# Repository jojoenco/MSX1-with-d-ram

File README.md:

# MSX1-with-d-ram
MSX1 compatible machine with old fashion D-Ram

Specs:  
Z80  
TMS9918 (composiet out)  
8255  
AY-3-8910  
HM4816 X8 V-Ram  
HM4864 X8 Ram  
74xx  logic IC's  

Tested until version 2.5 
This is version 2.6 should work as I only removed the Opamp for audio out and chanced the Transistor for the (Cassete)relay that
probably nobody uses. (because there is also a jack in and out for the cassete)

What works and tested in version 2.5:
- [x] Boot with MSX-Bios and C-Bios 
- [x] Video Out
- [x] audio out (sound was bad in version 2.5 so removed Opamp in 2.6)
- [x] Joystick ports
- [x] cassete in through 3.5"mm jack
- [ ] cassete out not tested
- [ ] Cassete DIN not tested
- [ ] relay (for Cassete REM) did not switch in version 2.5 (chanced transistor but not tested yet)
- [x] reset
- [X] Keyboard 
- [X] Cartridge Slot 1 and Slot2
- [ ] Printer port not tested

Because there is only a matrix connection for the keyboard I used the keyboard from Sergey Kiselev (github.com/skiselev/omega) to test.
I used the keyboard without de chips on it because they are on the main board and I jumpered on U2 the pins 1-2 and 3-4 and 5-6 and 8-9.
And then connected the wires directly to U1 pin 1-9 and J1 the bottom row.

My own keyboard PCB is ready but I am waiting for the switches to test it.

THE KEYBOARD  
The switches came in and it works fine:  
https://github.com/jojoenco/Keyboard-for-MSX1-with-d-ram

Below a foto of version 2.0 

And more Below Version 2.6 with no components yet

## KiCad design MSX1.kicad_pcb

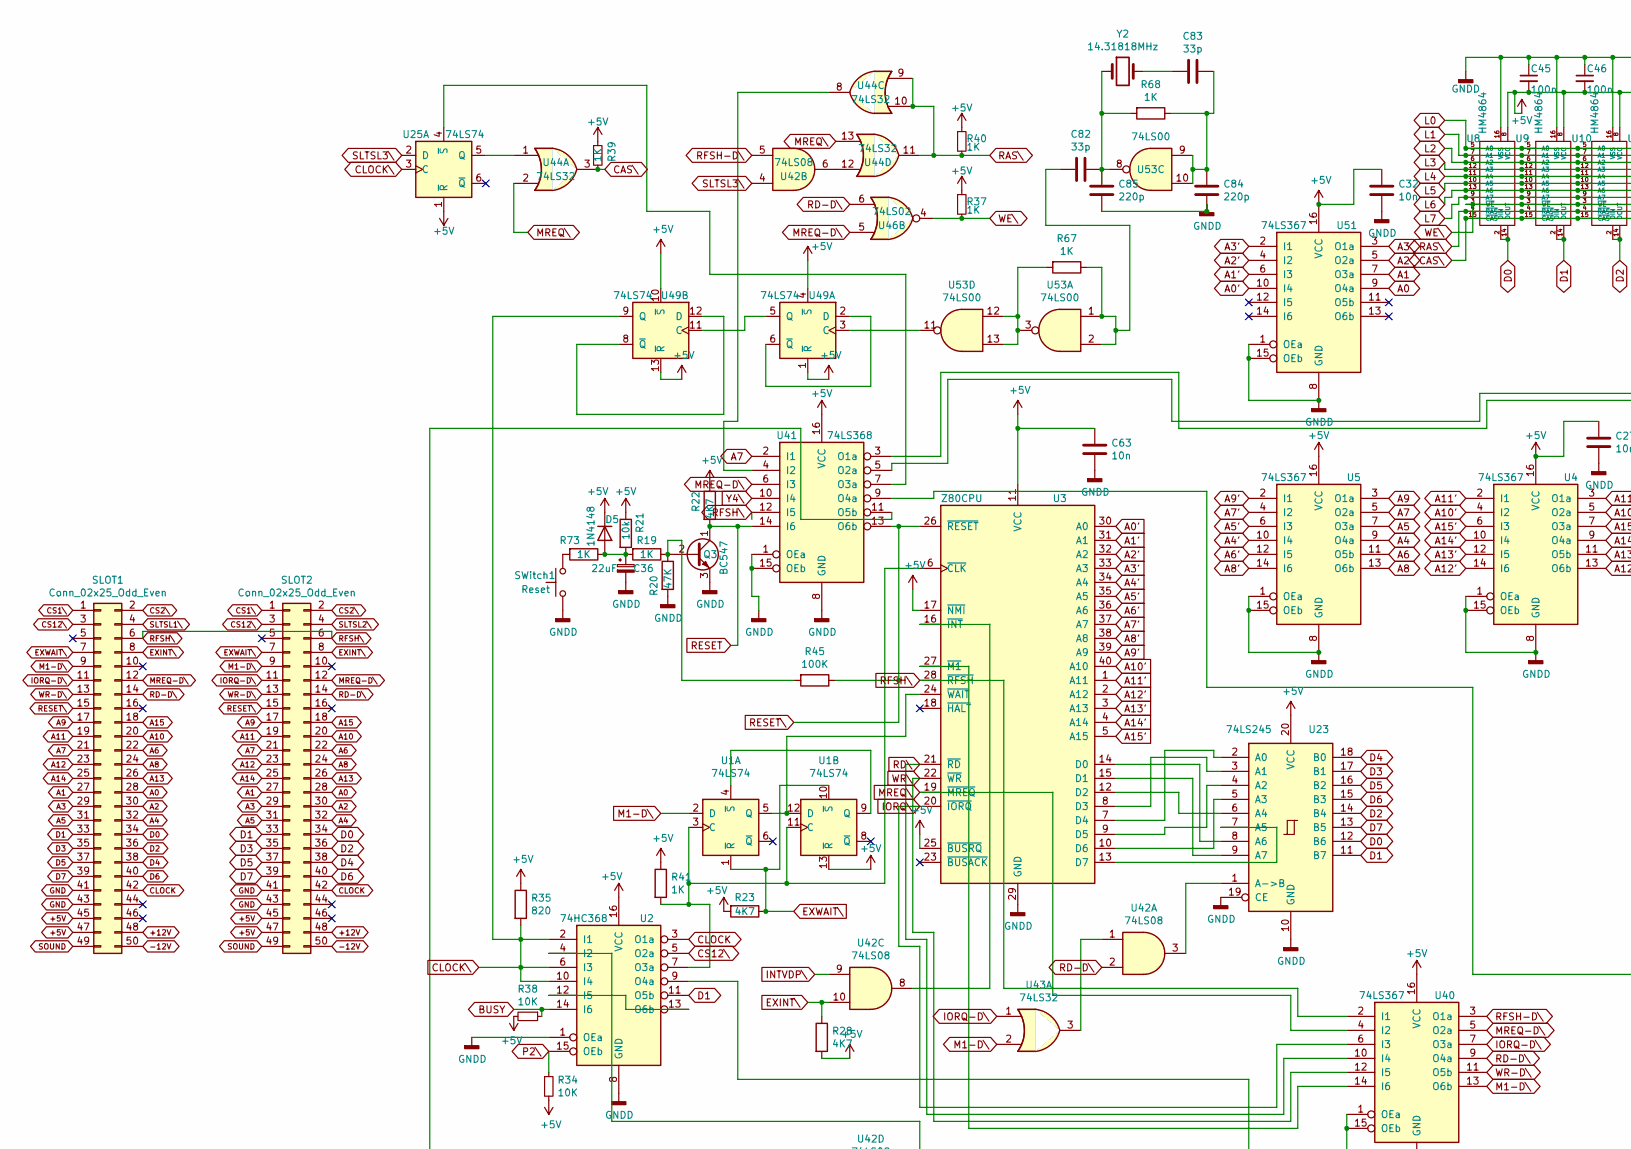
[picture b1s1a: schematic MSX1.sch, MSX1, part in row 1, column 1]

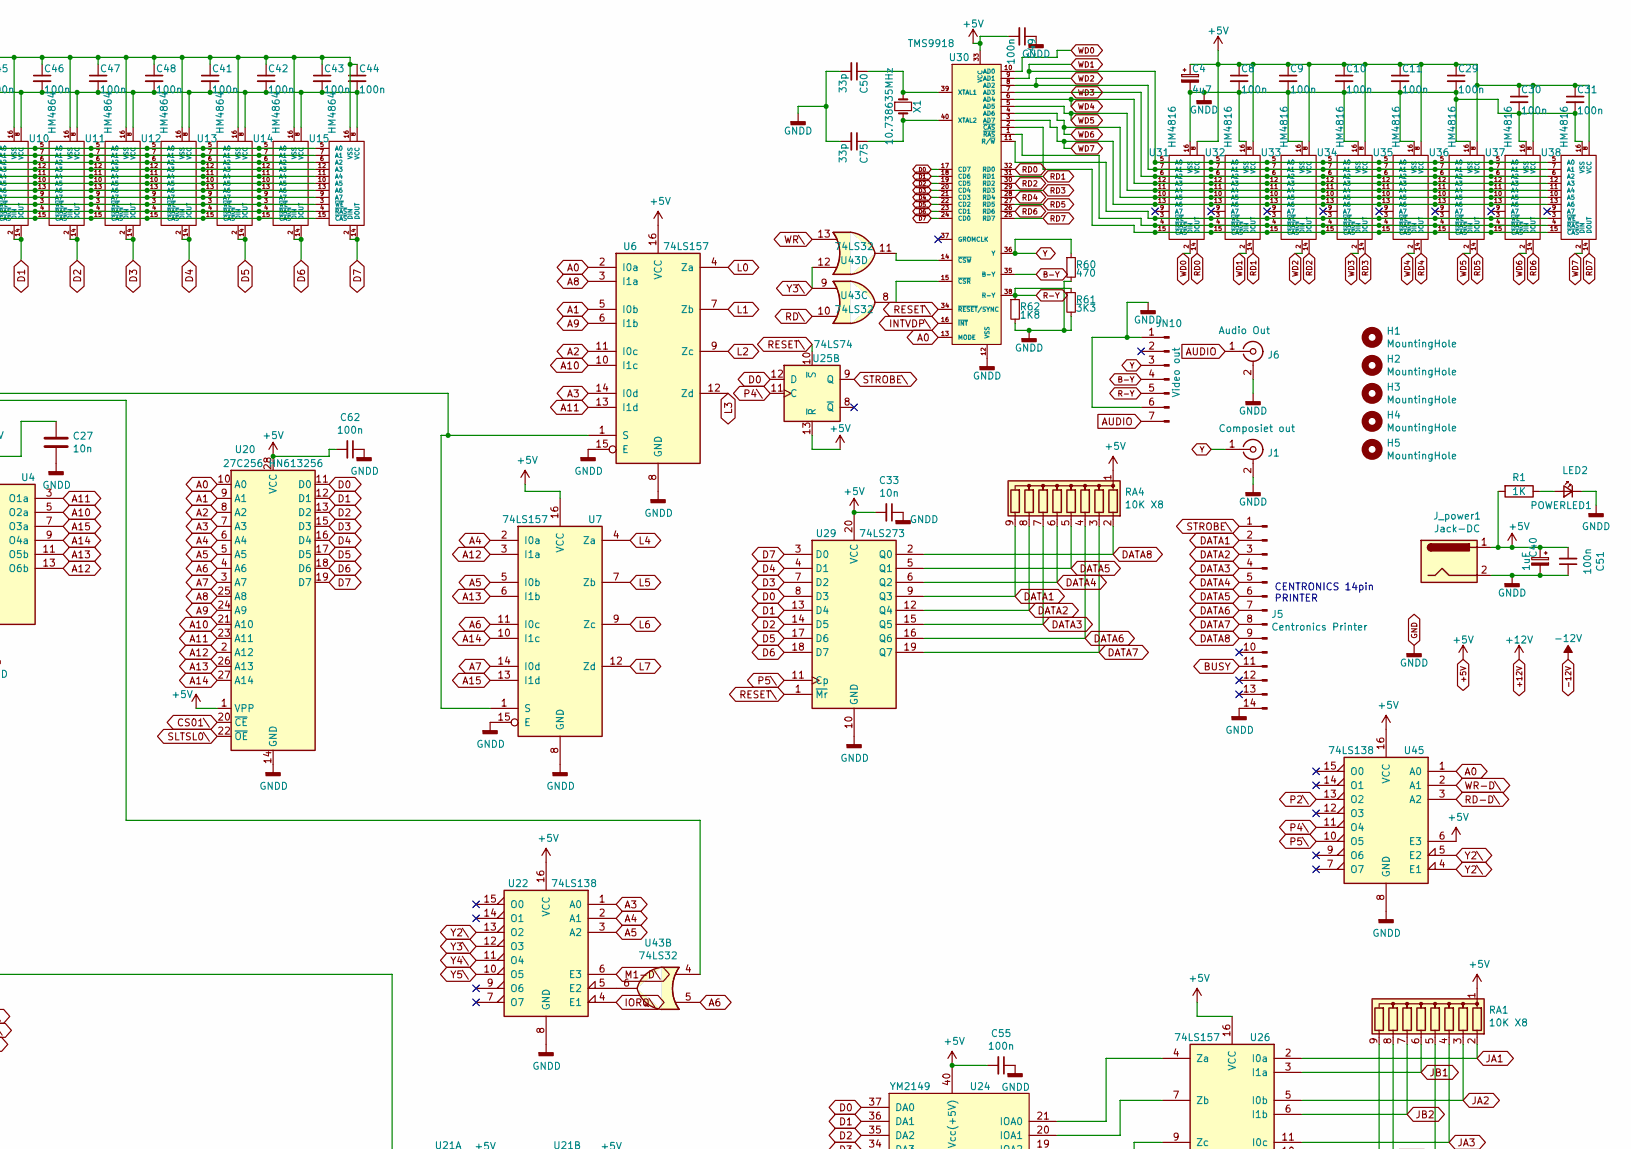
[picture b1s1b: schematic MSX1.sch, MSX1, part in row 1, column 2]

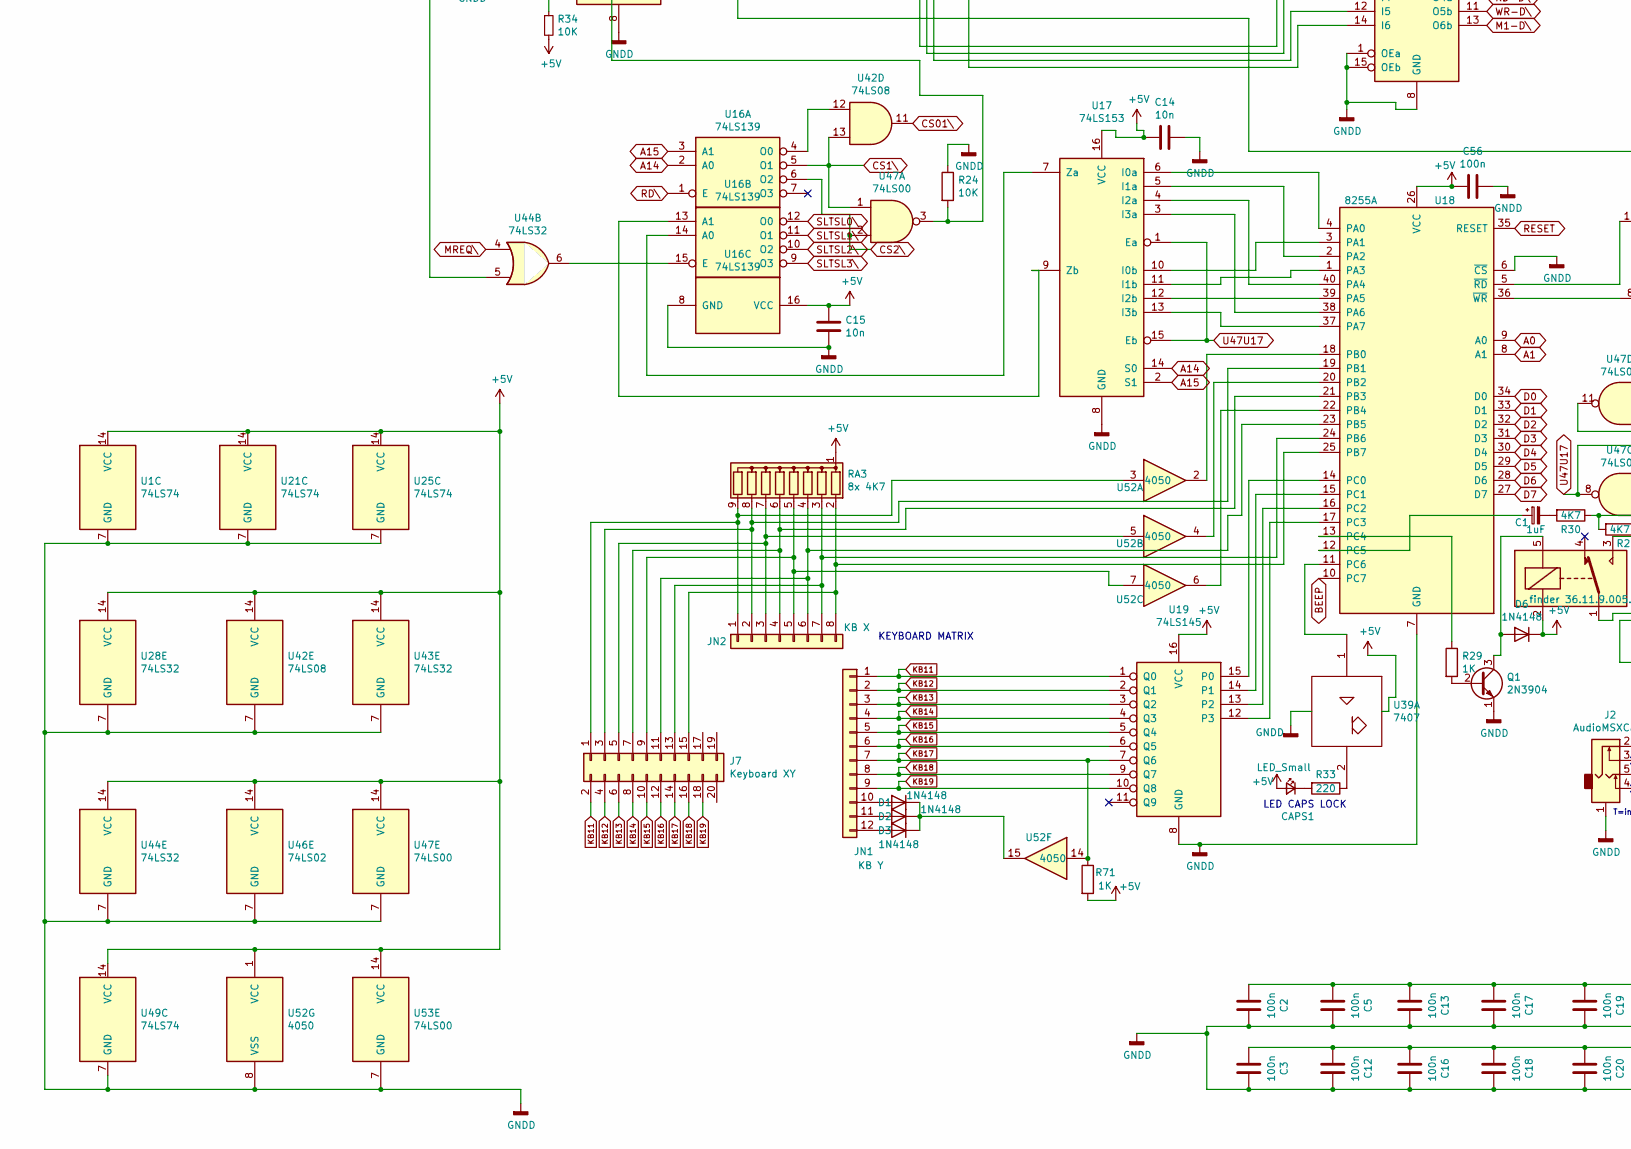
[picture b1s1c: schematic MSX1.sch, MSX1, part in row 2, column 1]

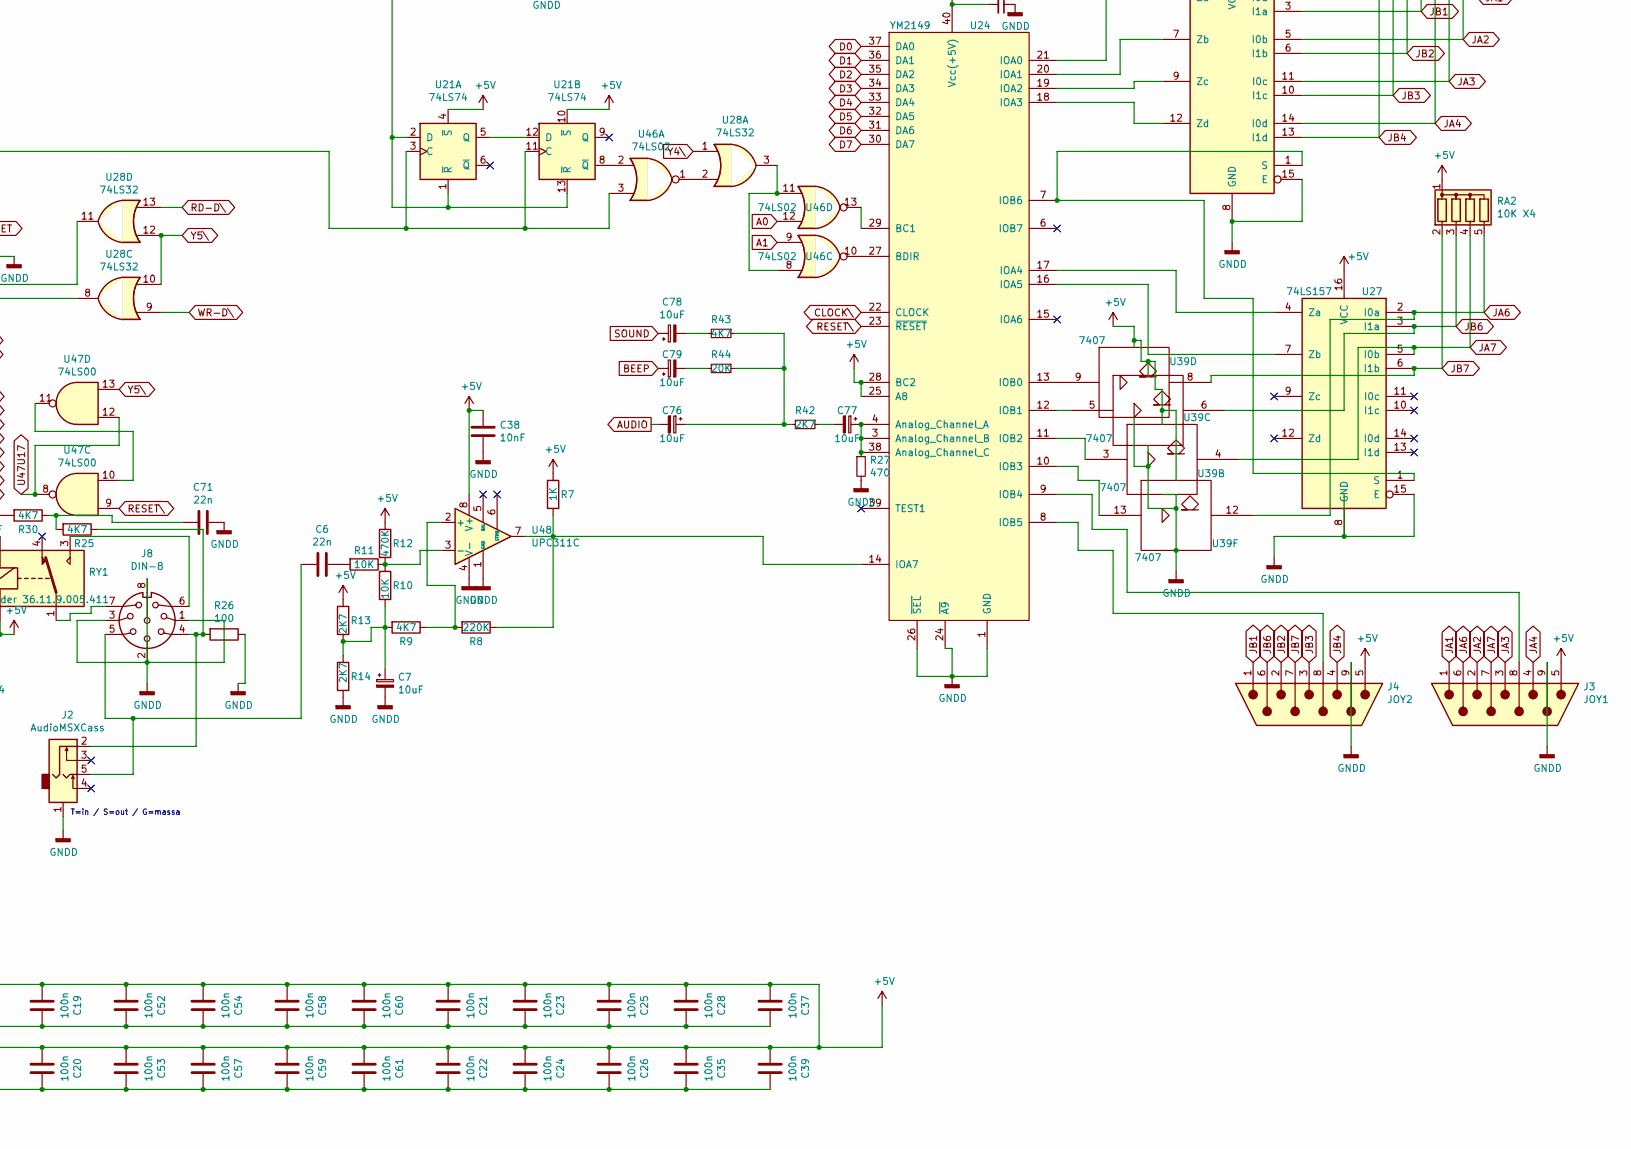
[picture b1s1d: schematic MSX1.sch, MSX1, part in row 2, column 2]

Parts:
C1, C40: 1uF; CP_Radial_D4.0mm_P1.50mm
C2, C3, C5, C8, C9, C10, C11, C12, C13, C16, C17, C18, C19, C20, C21, C22, C23, C24, C25, C26, C28, C29, C30, C31, C35, C37, C39, C41, C42, C43, C44, C45, C46, C47, C48, C49, C51, C52, C53, C54, C55, C56, C57, C58, C59, C60, C61, C62: 100n; C_Disc_D4.3mm_W1.9mm_P5.00mm
C4: 4u7; CP_Radial_D4.0mm_P1.50mm
C6, C71: 22n; C_Disc_D4.3mm_W1.9mm_P5.00mm
C7, C76, C77, C78, C79: 10uF; CP_Radial_D4.0mm_P1.50mm
C14, C15, C27, C32, C33, C63: 10n; C_Disc_D4.3mm_W1.9mm_P5.00mm
C36: 22uF; CP_Radial_D4.0mm_P1.50mm
C38: 10nF; C_Disc_D4.3mm_W1.9mm_P5.00mm
C50, C75, C82, C83: 33p; C_Disc_D4.3mm_W1.9mm_P5.00mm
C84, C85: 220p; C_Disc_D4.3mm_W1.9mm_P5.00mm
CAPS1: LED_Small; LED_D5.0mm
D1, D2, D3, D5, D6: 1N4148; D_A-405_P7.62mm_Horizontal
H1, H2, H3, H4, H5: MountingHole; MountingHole_4.3mm_M4
J1: Composiet out; RCA FeMale
J2: AudioMSXCass; Jack_conn_audio
J3: JOY1; DSUB-9_Male_Horizontal_Pitch2.77x2.84mm_EdgePinOffset4.94mm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
J4: JOY2; DSUB-9_Male_Horizontal_Pitch2.77x2.84mm_EdgePinOffset4.94mm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
J5: Centronics Printer; Multicomp_MC9A12-1434_2x07x2.54mm_Straight
J6: Audio Out; RCA FeMale
J7: Keyboard XY; IDC-Header_2x10_P2.54mm_Vertical
J8: DIN-8; DIN 8 PIN 270gr round Chassis
JN1: KB Y; Pin_Header_Straight_1x12_Pitch2.54mm
JN2: KB X; Pin_Header_Straight_1x08_Pitch2.54mm
JN10: Video out; Pin_Header_Straight_1x07_Pitch2.54mm
J_power1: Jack-DC; BarrelJack_Wuerth_6941xx301002
POWERLED1: LED2; LED_D5.0mm
Q1: 2N3904; TO-92
Q3: BC547; TO-92
R1, R7, R19, R29, R37, R39, R40, R41, R67, R68, R71, R73: 1K; R_Axial_DIN0207_L6.3mm_D2.5mm_P7.62mm_Horizontal
R8: 220K; R_Axial_DIN0207_L6.3mm_D2.5mm_P7.62mm_Horizontal
R9, R22, R23, R25, R28, R30, R43: 4K7; R_Axial_DIN0207_L6.3mm_D2.5mm_P7.62mm_Horizontal
R10, R11, R24, R34, R38: 10K; R_Axial_DIN0207_L6.3mm_D2.5mm_P7.62mm_Horizontal
R12: 470K; R_Axial_DIN0207_L6.3mm_D2.5mm_P7.62mm_Horizontal
R13, R14, R42: 2K7; R_Axial_DIN0207_L6.3mm_D2.5mm_P7.62mm_Horizontal
R20: 47K; R_Axial_DIN0207_L6.3mm_D2.5mm_P7.62mm_Horizontal
R21: 10k; R_Axial_DIN0207_L6.3mm_D2.5mm_P7.62mm_Horizontal
R26: 100; R_Axial_DIN0207_L6.3mm_D2.5mm_P7.62mm_Horizontal
R27, R60: 470; R_Axial_DIN0207_L6.3mm_D2.5mm_P7.62mm_Horizontal
R33: 220; R_Axial_DIN0207_L6.3mm_D2.5mm_P7.62mm_Horizontal
R35: 820; R_Axial_DIN0207_L6.3mm_D2.5mm_P7.62mm_Horizontal
R44: 20K; R_Axial_DIN0207_L6.3mm_D2.5mm_P7.62mm_Horizontal
R45: 100K; R_Axial_DIN0207_L6.3mm_D2.5mm_P7.62mm_Horizontal
R61: 3K3; R_Axial_DIN0207_L6.3mm_D2.5mm_P7.62mm_Horizontal
R62: 1K8; R_Axial_DIN0207_L6.3mm_D2.5mm_P7.62mm_Horizontal
RA1, RA4: 10K X8; R_Array_SIP9
RA2: 10K X4; R_Array_SIP5
RA3: 8x 4K7; R_Array_SIP9
RY1: finder 36.11.9.005.411; Relay_SPDT_OMRON-G5LE-1
SLOT1, SLOT2: Conn_02x25_Odd_Even; Slot_conn
SWitch1: Reset; SW_Tactile_SPST_Angled_PTS645Vx39-2LFS
U1, U21, U25, U49: 74LS74; DIP-14_W7.62mm_Socket
U2: 74HC368; DIP-16_W7.62mm_Socket
U3: Z80CPU; DIP-40_W15.24mm
U4, U5, U40, U51: 74LS367; DIP-16_W7.62mm_Socket
U6, U7, U26, U27: 74LS157; DIP-16_W7.62mm_Socket
U8, U9, U10, U11, U12, U13, U14, U15: HM4864; DIP-16_W7.62mm_Socket
U16: 74LS139; DIP-16_W7.62mm_Socket
U17: 74LS153; DIP-16_W7.62mm_Socket
U18: 8255A; DIP-40_W15.24mm_Socket
U19: 74LS145; DIP-16_W7.62mm_Socket
U20: 27C256 HN613256; DIP-28_W15.24mm_Socket
U22, U45: 74LS138; DIP-16_W7.62mm_Socket
U23: 74LS245; DIP-20_W7.62mm_Socket
U24: YM2149; DIP-40_W15.24mm
U28, U43, U44: 74LS32; DIP-14_W7.62mm_Socket
U29: 74LS273; DIP-20_W7.62mm_Socket
U30: TMS9918; DIP-40_W15.24mm
U31, U32, U33, U34, U35, U36, U37, U38: HM4816; DIP-16_W7.62mm_Socket
U39: 7407; DIP-14_W7.62mm_Socket
U41: 74LS368; DIP-16_W7.62mm_Socket
U42: 74LS08; DIP-14_W7.62mm_Socket
U46: 74LS02; DIP-14_W7.62mm_Socket
U47, U53: 74LS00; DIP-14_W7.62mm_Socket
U48: UPC311C; DIP-8_W7.62mm_Socket
U52: 4050; DIP-16_W7.62mm_Socket
X1: 10.738635MHz; Crystal_HC49-4H_Vertical
Y2: 14.31818MHz; Crystal_HC49-4H_Vertical

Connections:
+5V: C2.2, C3.2, C4.1, C5.2, C8.1, C9.1, C10.1, C11.1, C12.2, C13.2, C14.2, C15.1, C16.2, C17.2, C18.2, C19.2, C20.2, C21.2, C22.2, C23.2, C24.2, C25.2, C26.2, C27.1, C28.2, C29.1, C30.1, C31.1, C32.1, C33.2, C35.2, C37.2, C38.1, C39.2, C40.1, C41.2, C42.2, C43.2, C44.2, C45.2, C46.2, C47.2, C48.2, C49.2, C51.2, C52.2, C53.2, C54.2, C55.2, C56.2, C57.2, C58.2, C59.2, C60.2, C61.2, C62.2, C63.1, CAPS1.2 (A), D5.1 (K), D6.1 (K), J3.5, J4.5, J_power1.1, R1.2, R7.1, R12.1, R13.1, R21.1, R22.1, R23.2, R28.2, R34.2, R35.1, R37.1, R38.2, R39.1, R40.1, R41.1, R71.2, RA1.1 (common), RA2.1 (common), RA3.1 (common), RA4.1 (common), RY1.2, SLOT1.45, SLOT1.47, SLOT2.45, SLOT2.47, U1.13 (~R), U1.14 (VCC), U2.16 (VCC), U3.11 (VCC), U3.17 (~NMI~), U3.25 (~BUSRQ~), U4.16 (VCC), U5.16 (VCC), U6.16 (VCC), U7.16 (VCC), U8.8 (VCC), U9.8 (VCC), U10.8 (VCC), U11.8 (VCC), U12.8 (VCC), U13.8 (VCC), U14.8 (VCC), U15.8 (VCC), U16.16 (VCC), U17.16 (VCC), U18.26 (VCC), U19.16 (VCC), U20.1 (VPP), U20.28 (VCC), U21.4 (~S), U21.10 (~S), U21.14 (VCC), U22.16 (VCC), U23.20 (VCC), U24.25 (A8), U24.28 (BC2), U24.40 (Vcc(+5V)), U25.1 (~R), U25.13 (~R), U25.14 (VCC), U26.16 (VCC), U27.16 (VCC), U28.14 (VCC), U29.20 (VCC), U30.33 (VCC), U31.8 (VCC), U32.8 (VCC), U33.8 (VCC), U34.8 (VCC), U35.8 (VCC), U36.8 (VCC), U37.8 (VCC), U38.8 (VCC), U39.14 (VCC), U40.16 (VCC), U41.16 (VCC), U42.14 (VCC), U43.14 (VCC), U44.14 (VCC), U45.6 (E3), U45.16 (VCC), U46.14 (VCC), U47.14 (VCC), U48.8 (V+), U49.1 (~R), U49.4 (~S), U49.10 (~S), U49.13 (~R), U49.14 (VCC), U51.16 (VCC), U52.1 (VCC), U53.14 (VCC)
+12V: SLOT1.48, SLOT2.48
-12V: SLOT1.50, SLOT2.50
A0: SLOT1.28, SLOT2.28, U6.2 (I0a), U18.9 (A0), U20.10 (A0), U30.13 (MODE), U45.1 (A0), U46.12, U51.9 (O4a)
A0': U3.30 (A0), U51.10 (I4)
A1: SLOT1.27, SLOT2.27, U6.5 (I0b), U18.8 (A1), U20.9 (A1), U46.9, U51.7 (O3a)
A1': U3.31 (A1), U51.6 (I3)
A2: SLOT1.30, SLOT2.30, U6.11 (I0c), U20.8 (A2), U51.5 (O2a)
A2': U3.32 (A2), U51.4 (I2)
A3: SLOT1.29, SLOT2.29, U6.14 (I0d), U20.7 (A3), U22.1 (A0), U51.3 (O1a)
A3': U3.33 (A3), U51.2 (I1)
A4: SLOT1.32, SLOT2.32, U5.9 (O4a), U7.2 (I0a), U20.6 (A4), U22.2 (A1)
A4': U3.34 (A4), U5.10 (I4)
A5: SLOT1.31, SLOT2.31, U5.7 (O3a), U7.5 (I0b), U20.5 (A5), U22.3 (A2)
A5': U3.35 (A5), U5.6 (I3)
A6: SLOT1.22, SLOT2.22, U5.11 (O5b), U7.11 (I0c), U20.4 (A6), U43.5
A6': U3.36 (A6), U5.12 (I5)
A7: SLOT1.21, SLOT2.21, U5.5 (O2a), U7.14 (I0d), U20.3 (A7), U41.2 (I1)
A7': U3.37 (A7), U5.4 (I2)
A8: SLOT1.24, SLOT2.24, U5.13 (O6b), U6.3 (I1a), U20.25 (A8)
A8': U3.38 (A8), U5.14 (I6)
A9: SLOT1.17, SLOT2.17, U5.3 (O1a), U6.6 (I1b), U20.24 (A9)
A9': U3.39 (A9), U5.2 (I1)
A10: SLOT1.20, SLOT2.20, U4.5 (O2a), U6.10 (I1c), U20.21 (A10)
A10': U3.40 (A10), U4.4 (I2)
A11: SLOT1.19, SLOT2.19, U4.3 (O1a), U6.13 (I1d), U20.23 (A11)
A11': U3.1 (A11), U4.2 (I1)
A12: SLOT1.23, SLOT2.23, U4.13 (O6b), U7.3 (I1a), U20.2 (A12)
A12': U3.2 (A12), U4.14 (I6)
A13: SLOT1.26, SLOT2.26, U4.11 (O5b), U7.6 (I1b), U20.26 (A13)
A13': U3.3 (A13), U4.12 (I5)
A14: SLOT1.25, SLOT2.25, U4.9 (O4a), U7.10 (I1c), U16.2 (A0), U17.14 (S0), U20.27 (A14)
A14': U3.4 (A14), U4.10 (I4)
A15: SLOT1.18, SLOT2.18, U4.7 (O3a), U7.13 (I1d), U16.3 (A1), U17.2 (S1)
A15': U3.5 (A15), U4.6 (I3)
AUDIO: C76.2, J6.1 (In), JN10.7
B-Y: JN10.4, U30.35 (B-Y)
BEEP: C79.1, U18.10 (PC7)
BUSY: J5.11, R38.1, U2.14 (I6)
CAS\: R39.2, U8.15 (~CAS), U9.15 (~CAS), U10.15 (~CAS), U11.15 (~CAS), U12.15 (~CAS), U13.15 (~CAS), U14.15 (~CAS), U15.15 (~CAS), U44.3
CLOCK: SLOT1.42, SLOT2.42, U2.3 (O1a)
CLOCK\: R35.2, U2.2 (I1), U2.6 (I3), U2.10 (I4), U24.22 (CLOCK), U25.3 (C), U49.9 (Q)
CS1\: SLOT1.1, SLOT2.1, U16.5 (O1), U42.13, U47.1
CS01\: U20.20 (~CE), U42.11
CS2\: SLOT1.2, SLOT2.2, U16.6 (O2), U47.2
CS12\: SLOT1.3, SLOT2.3, U2.5 (O2a)
D0: SLOT1.34, SLOT2.34, U8.2 (DIN), U8.14 (DOUT), U18.34 (D0), U20.11 (D0), U23.12 (B6), U24.37 (DA0), U25.12 (D), U29.8 (D3), U30.17 (CD7)
D1: SLOT1.33, SLOT2.33, U2.11 (O5b), U9.2 (DIN), U9.14 (DOUT), U18.33 (D1), U20.12 (D1), U23.11 (B7), U24.36 (DA1), U29.13 (D4), U30.18 (CD6)
D2: SLOT1.36, SLOT2.36, U10.2 (DIN), U10.14 (DOUT), U18.32 (D2), U20.13 (D2), U23.14 (B4), U24.35 (DA2), U29.14 (D5), U30.19 (CD5)
D3: SLOT1.35, SLOT2.35, U11.2 (DIN), U11.14 (DOUT), U18.31 (D3), U20.15 (D3), U23.17 (B1), U24.34 (DA3), U29.7 (D2), U30.20 (CD4)
D4: SLOT1.38, SLOT2.38, U12.2 (DIN), U12.14 (DOUT), U18.30 (D4), U20.16 (D4), U23.18 (B0), U24.33 (DA4), U29.4 (D1), U30.21 (CD3)
D5: SLOT1.37, SLOT2.37, U13.2 (DIN), U13.14 (DOUT), U18.29 (D5), U20.17 (D5), U23.16 (B2), U24.32 (DA5), U29.17 (D6), U30.22 (CD2)
D6: SLOT1.40, SLOT2.40, U14.2 (DIN), U14.14 (DOUT), U18.28 (D6), U20.18 (D6), U23.15 (B3), U24.31 (DA6), U29.18 (D7), U30.23 (CD1)
D7: SLOT1.39, SLOT2.39, U15.2 (DIN), U15.14 (DOUT), U18.27 (D7), U20.19 (D7), U23.13 (B5), U24.30 (DA7), U29.3 (D0), U30.24 (CD0)
DATA1: J5.2, RA4.9 (R8), U29.9 (Q3)
DATA2: J5.3, RA4.8 (R7), U29.12 (Q4)
DATA3: J5.4, RA4.7 (R6), U29.15 (Q5)
DATA4: J5.5, RA4.6 (R5), U29.6 (Q2)
DATA5: J5.6, RA4.5 (R4), U29.5 (Q1)
DATA6: J5.7, RA4.4 (R3), U29.16 (Q6)
DATA7: J5.8, RA4.3 (R2), U29.19 (Q7)
DATA8: J5.9, RA4.2 (R1), U29.2 (Q0)
EXINT\: R28.1, SLOT1.8, SLOT2.8, U42.10
EXWAIT\: R23.1, SLOT1.7, SLOT2.7, U1.1 (~R), U1.10 (~S)
GND: C2.1, C3.1, C4.2, C5.1, C7.2, C8.2, C9.2, C10.2, C11.2, C12.1, C13.1, C14.1, C15.2, C16.1, C17.1, C18.1, C19.1, C20.1, C21.1, C22.1, C23.1, C24.1, C25.1, C26.1, C27.2, C28.1, C29.2, C30.2, C31.2, C32.2, C33.1, C35.1, C36.2, C37.1, C38.2, C39.1, C40.2, C41.1, C42.1, C43.1, C44.1, C45.1, C46.1, C47.1, C48.1, C49.1, C50.2, C51.1, C52.1, C53.1, C54.1, C55.1, C56.1, C57.1, C58.1, C59.1, C60.1, C61.1, C62.1, C63.2, C71.1, C75.2, C84.2, C85.2, J1.2 (Ext), J2.1, J3.9, J4.9, J5.14, J6.2 (Ext), J8.1, J8.2, J8.3, J8.8, JN10.1, JN10.6, J_power1.2, POWERLED1.1 (K), Q1.1 (E), Q3.3 (E), R14.2, R20.2, R24.1, R26.1, R27.2, R60.2, R61.2, R62.2, SLOT1.41, SLOT1.43, SLOT2.41, SLOT2.43, SWitch1.1, U1.7 (GND), U2.1 (OEa), U2.8 (GND), U3.29 (GND), U4.1 (OEa), U4.8 (GND), U4.15 (OEb), U5.1 (OEa), U5.8 (GND), U5.15 (OEb), U6.8 (GND), U6.15 (E), U7.8 (GND), U7.15 (E), U8.16 (VSS), U9.16 (VSS), U10.16 (VSS), U11.16 (VSS), U12.16 (VSS), U13.16 (VSS), U14.16 (VSS), U15.16 (VSS), U16.8 (GND), U17.8 (GND), U18.6 (~CS~), U18.7 (GND), U19.8 (GND), U20.14 (GND), U21.7 (GND), U22.8 (GND), U23.10 (GND), U23.19 (CE), U24.1 (GND), U24.24 (~A9), U24.26 (~SEL), U25.7 (GND), U26.8 (GND), U26.15 (E), U27.8 (GND), U27.15 (E), U28.7 (GND), U29.10 (GND), U30.12 (VSS), U31.16 (VSS), U32.16 (VSS), U33.16 (VSS), U34.16 (VSS), U35.16 (VSS), U36.16 (VSS), U37.16 (VSS), U38.16 (VSS), U39.7 (GND), U40.1 (OEa), U40.8 (GND), U40.15 (OEb), U41.1 (OEa), U41.8 (GND), U41.15 (OEb), U42.7 (GND), U43.7 (GND), U44.7 (GND), U45.8 (GND), U46.7 (GND), U47.7 (GND), U48.1 (GND), U48.4 (V-), U49.7 (GND), U51.1 (OEa), U51.8 (GND), U51.15 (OEb), U52.8 (VSS), U53.7 (GND)
INTVDP\: U30.16 (~INT), U42.9
IORQ-D\: SLOT1.11, SLOT2.11, U40.7 (O3a), U43.1
IORQ\: U3.20 (~IORQ~), U22.4 (E1), U40.6 (I3)
JA1: J3.1, RA1.2 (R1), U26.2 (I0a)
JA2: J3.2, RA1.3 (R2), U26.5 (I0b)
JA3: J3.3, RA1.4 (R3), U26.11 (I0c)
JA4: J3.4, RA1.5 (R4), U26.14 (I0d)
JA6: J3.6, RA2.5 (R4), U27.2 (I0a), U39.12
JA7: J3.7, RA2.4 (R3), U27.5 (I0b), U39.4
JB1: J4.1, RA1.6 (R5), U26.3 (I1a)
JB2: J4.2, RA1.7 (R6), U26.6 (I1b)
JB3: J4.3, RA1.8 (R7), U26.10 (I1c)
JB4: J4.4, RA1.9 (R8), U26.13 (I1d)
JB6: J4.6, RA2.3 (R2), U27.3 (I1a), U39.6
JB7: J4.7, RA2.2 (R1), U27.6 (I1b), U39.8
KB11: J7.2, JN1.1, U19.1 (Q0)
KB12: J7.4, JN1.2, U19.2 (Q1)
KB13: J7.6, JN1.3, U19.3 (Q2)
KB14: J7.8, JN1.4, U19.4 (Q3)
KB15: J7.10, JN1.5, U19.5 (Q4)
KB16: J7.12, JN1.6, U19.6 (Q5)
KB17: J7.14, JN1.7, R71.1, U19.7 (Q6), U52.14
KB18: J7.16, JN1.8, U19.9 (Q7)
KB19: J7.18, JN1.9, U19.10 (Q8)
L0: U6.4 (Za), U8.5 (A0), U9.5 (A0), U10.5 (A0), U11.5 (A0), U12.5 (A0), U13.5 (A0), U14.5 (A0), U15.5 (A0)
L1: U6.7 (Zb), U8.7 (A1), U9.7 (A1), U10.7 (A1), U11.7 (A1), U12.7 (A1), U13.7 (A1), U14.7 (A1), U15.7 (A1)
L2: U6.9 (Zc), U8.6 (A2), U9.6 (A2), U10.6 (A2), U11.6 (A2), U12.6 (A2), U13.6 (A2), U14.6 (A2), U15.6 (A2)
L3: U6.12 (Zd), U8.12 (A3), U9.12 (A3), U10.12 (A3), U11.12 (A3), U12.12 (A3), U13.12 (A3), U14.12 (A3), U15.12 (A3)
L4: U7.4 (Za), U8.11 (A4), U9.11 (A4), U10.11 (A4), U11.11 (A4), U12.11 (A4), U13.11 (A4), U14.11 (A4), U15.11 (A4)
L5: U7.7 (Zb), U8.10 (A5), U9.10 (A5), U10.10 (A5), U11.10 (A5), U12.10 (A5), U13.10 (A5), U14.10 (A5), U15.10 (A5)
L6: U7.9 (Zc), U8.13 (A6), U9.13 (A6), U10.13 (A6), U11.13 (A6), U12.13 (A6), U13.13 (A6), U14.13 (A6), U15.13 (A6)
L7: U7.12 (Zd), U8.9 (A7), U9.9 (A7), U10.9 (A7), U11.9 (A7), U12.9 (A7), U13.9 (A7), U14.9 (A7), U15.9 (A7)
M1-D\: SLOT1.9, SLOT2.9, U1.2 (D), U22.6 (E3), U40.13 (O6b), U43.2
MREQ-D\: SLOT1.12, SLOT2.12, U40.5 (O2a), U41.6 (I3), U46.5
MREQ\: U3.19 (~MREQ~), U40.4 (I2), U44.2, U44.4, U44.13
unnamed: C1.1, U18.12 (PC5)
unnamed: C1.2, R30.2
unnamed: C6.1, R11.2
unnamed: C6.2, J2.5, J8.5
unnamed: C7.1, R9.2, R10.2, R13.2, R14.1
unnamed: C36.1, D5.2 (A), R19.2, R21.2, R73.1
unnamed: C50.1, U30.39 (XTAL1), X1.1
unnamed: C71.2, R25.2, R30.1
unnamed: C75.1, U30.40 (XTAL2), X1.2
unnamed: C76.1, R42.2, R43.1, R44.1
unnamed: C77.1, R27.1, U24.3 (Analog_Channel_B), U24.4 (Analog_Channel_A), U24.38 (Analog_Channel_C)
unnamed: C77.2, R42.1
unnamed: C78.2, R43.2
unnamed: C79.2, R44.2
unnamed: C82.1, C85.1, R68.2, U53.8, Y2.1
unnamed: C82.2, R67.1, U53.1, U53.2
unnamed: C83.1, C84.1, R68.1, U53.9, U53.10
unnamed: C83.2, Y2.2
unnamed: CAPS1.1 (K), R33.2
unnamed: D1.1 (K), D2.1 (K), D3.1 (K), U52.15
unnamed: D1.2 (A), JN1.10
unnamed: D2.2 (A), JN1.11
unnamed: D3.2 (A), JN1.12
unnamed: D6.2 (A), Q1.3 (C), RY1.5
unnamed: J2.2, J8.4, R25.1, R26.2
unnamed: J3.8, U24.9 (IOB4)
unnamed: J4.8, U24.8 (IOB5)
unnamed: J7.1, JN2.1, RA3.9 (R8), U52.3
unnamed: J7.3, JN2.2, RA3.8 (R7), U18.19 (PB1)
unnamed: J7.5, JN2.3, RA3.7 (R6), U52.5
unnamed: J7.7, JN2.4, RA3.6 (R5), U18.21 (PB3)
unnamed: J7.9, JN2.5, RA3.5 (R4), U52.7
unnamed: J7.11, JN2.6, RA3.4 (R3), U18.23 (PB5)
unnamed: J7.13, JN2.7, RA3.3 (R2), U18.24 (PB6)
unnamed: J7.15, JN2.8, RA3.2 (R1), U18.25 (PB7)
unnamed: J8.6, RY1.3
unnamed: J8.7, RY1.1
unnamed: POWERLED1.2 (A), R1.1
unnamed: Q1.2 (B), R29.2
unnamed: Q3.2 (B), R19.1, R20.1, R45.2
unnamed: R7.2, R8.1, U24.14 (IOA7), U48.7
unnamed: R8.2, R9.1, U48.2 (+)
unnamed: R10.1, R11.1, R12.2, U48.3 (-)
unnamed: R24.2, U2.4 (I2), U47.3
unnamed: R29.1, U18.13 (PC4)
unnamed: R33.1, U39.2
unnamed: R41.2, U1.3 (C), U1.11 (C), U2.7 (O3a), U3.6 (~CLK~)
unnamed: R67.2, U53.3, U53.12, U53.13
unnamed: R73.2, SWitch1.2
unnamed: U1.4 (~S), U1.9 (Q)
unnamed: U1.5 (Q), U1.12 (D), U3.24 (~WAIT~)
unnamed: U2.9 (O4a), U21.3 (C), U21.11 (C), U46.3
unnamed: U2.12 (I5), U2.13 (O6b)
unnamed: U3.16 (~INT~), U42.8
unnamed: U3.27 (~M1~), U40.14 (I6)
unnamed: U16.4 (O0), U42.12
unnamed: U16.13 (A1), U17.9 (Zb)
unnamed: U16.14 (A0), U17.7 (Za)
unnamed: U16.15 (E), U44.6
unnamed: U17.3 (I3a), U18.38 (PA6)
unnamed: U17.4 (I2a), U18.40 (PA4)
unnamed: U17.5 (I1a), U18.2 (PA2)
unnamed: U17.6 (I0a), U18.4 (PA0)
unnamed: U17.10 (I0b), U18.3 (PA1)
unnamed: U17.11 (I1b), U18.1 (PA3)
unnamed: U17.12 (I2b), U18.39 (PA5)
unnamed: U17.13 (I3b), U18.37 (PA7)
unnamed: U18.5 (~RD~), U28.11
unnamed: U18.11 (PC6), U39.1
unnamed: U18.14 (PC0), U19.15 (P0)
unnamed: U18.15 (PC1), U19.14 (P1)
unnamed: U18.16 (PC2), U19.13 (P2)
unnamed: U18.17 (PC3), U19.12 (P3)
unnamed: U18.18 (PB0), U52.2
unnamed: U18.20 (PB2), U52.4
unnamed: U18.22 (PB4), U52.6
unnamed: U18.36 (~WR~), U28.8
unnamed: U21.1 (~R), U21.2 (D), U21.13 (~R), U41.9 (O4a)
unnamed: U21.8 (~Q), U46.2
unnamed: U21.5 (Q), U21.12 (D)
unnamed: U22.5 (E2), U43.6
unnamed: U23.1 (A->B), U42.3
unnamed: U3.7 (D4), U23.2 (A0)
unnamed: U3.8 (D3), U23.3 (A1)
unnamed: U3.9 (D5), U23.4 (A2)
unnamed: U3.10 (D6), U23.5 (A3)
unnamed: U3.12 (D2), U23.6 (A4)
unnamed: U3.13 (D7), U23.7 (A5)
unnamed: U3.14 (D0), U23.8 (A6)
unnamed: U3.15 (D1), U23.9 (A7)
unnamed: U24.7 (IOB6), U26.1 (S), U27.1 (S)
unnamed: U24.10 (IOB3), U39.13
unnamed: U24.11 (IOB2), U39.3
unnamed: U24.12 (IOB1), U39.5
unnamed: U24.13 (IOB0), U39.9
unnamed: U24.16 (IOA5), U27.7 (Zb)
unnamed: U24.17 (IOA4), U27.4 (Za)
unnamed: U24.18 (IOA3), U26.12 (Zd)
unnamed: U24.19 (IOA2), U26.9 (Zc)
unnamed: U24.20 (IOA1), U26.7 (Zb)
unnamed: U24.21 (IOA0), U26.4 (Za)
unnamed: U24.27 (BDIR), U46.10
unnamed: U24.29 (BC1), U46.13
unnamed: U25.4 (~S), U41.7 (O3a)
unnamed: U25.5 (Q), U44.1
unnamed: U28.2, U46.1
unnamed: U28.3, U46.8, U46.11
unnamed: U30.1 (~RAS), U31.4 (~RAS), U32.4 (~RAS), U33.4 (~RAS), U34.4 (~RAS), U35.4 (~RAS), U36.4 (~RAS), U37.4 (~RAS), U38.4 (~RAS)
unnamed: U30.2 (~CAS), U31.15 (~CAS), U32.15 (~CAS), U33.15 (~CAS), U34.15 (~CAS), U35.15 (~CAS), U36.15 (~CAS), U37.15 (~CAS), U38.15 (~CAS)
unnamed: U30.11 (R/~W), U31.3 (~WE), U32.3 (~WE), U33.3 (~WE), U34.3 (~WE), U35.3 (~WE), U36.3 (~WE), U37.3 (~WE), U38.3 (~WE)
unnamed: U30.14 (~CSW), U43.11
unnamed: U30.15 (~CSR), U43.8
unnamed: U41.3 (O1a), U43.4
unnamed: U41.4 (I2), U44.8
unnamed: U6.1 (S), U7.1 (S), U41.5 (O2a)
unnamed: U41.11 (O5b), U44.5
unnamed: U42.1, U43.3
unnamed: U42.6, U44.12
unnamed: U47.10, U47.11
unnamed: U49.2 (D), U49.6 (~Q)
unnamed: U49.3 (C), U53.11
unnamed: U49.5 (Q), U49.11 (C)
unnamed: U49.8 (~Q), U49.12 (D)
P2\: R34.1, U2.15 (OEb), U45.13 (O2)
P4\: U25.11 (C), U45.11 (O4)
P5\: U29.11 (Cp), U45.10 (O5)
R-Y: JN10.5, R61.1, R62.1, U30.38 (R-Y)
RAS\: R40.2, U8.4 (~RAS), U9.4 (~RAS), U10.4 (~RAS), U11.4 (~RAS), U12.4 (~RAS), U13.4 (~RAS), U14.4 (~RAS), U15.4 (~RAS), U44.9, U44.10, U44.11
RD0: U30.32 (RD0), U31.14 (DOUT)
RD1: U30.31 (RD1), U32.14 (DOUT)
RD2: U30.30 (RD2), U33.14 (DOUT)
RD3: U30.29 (RD3), U34.14 (DOUT)
RD4: U30.28 (RD4), U35.14 (DOUT)
RD5: U30.27 (RD5), U36.14 (DOUT)
RD6: U30.26 (RD6), U37.14 (DOUT)
RD7: U30.25 (RD7), U38.14 (DOUT)
RD-D\: SLOT1.14, SLOT2.14, U28.13, U40.9 (O4a), U42.2, U45.3 (A2), U46.6
RD\: U3.21 (~RD~), U16.1 (E), U40.10 (I4), U43.10
RESET: Q3.1 (C), R22.2, U18.35 (RESET), U41.14 (I6)
RESET\: R45.1, SLOT1.15, SLOT2.15, U3.26 (~RESET~), U24.23 (~RESET), U25.10 (~S), U29.1 (~Mr), U30.34 (~RESET~/SYNC), U41.13 (O6b), U47.9
RFSH-D\: U40.3 (O1a), U42.5
RFSH\: SLOT1.6, SLOT2.6, U3.28 (~RFSH~), U40.2 (I1), U41.12 (I5)
SLTSL0\: U16.12 (O0), U20.22 (~OE)
SLTSL1\: SLOT1.4, U16.11 (O1)
SLTSL2\: SLOT2.4, U16.10 (O2)
SLTSL3\: U16.9 (O3), U25.2 (D), U42.4
SOUND: C78.1, SLOT1.49, SLOT2.49
STROBE\: J5.1, U25.9 (Q)
U47U17: U17.1 (Ea), U17.15 (Eb), U47.8, U47.12
WD0: U30.10 (AD0), U31.2 (DIN)
WD1: U30.9 (AD1), U31.5 (A0), U32.2 (DIN), U32.5 (A0), U33.5 (A0), U34.5 (A0), U35.5 (A0), U36.5 (A0), U37.5 (A0), U38.5 (A0)
WD2: U30.8 (AD2), U31.7 (A1), U32.7 (A1), U33.2 (DIN), U33.7 (A1), U34.7 (A1), U35.7 (A1), U36.7 (A1), U37.7 (A1), U38.7 (A1)
WD3: U30.7 (AD3), U31.6 (A2), U32.6 (A2), U33.6 (A2), U34.2 (DIN), U34.6 (A2), U35.6 (A2), U36.6 (A2), U37.6 (A2), U38.6 (A2)
WD4: U30.6 (AD4), U31.12 (A3), U32.12 (A3), U33.12 (A3), U34.12 (A3), U35.2 (DIN), U35.12 (A3), U36.12 (A3), U37.12 (A3), U38.12 (A3)
WD5: U30.5 (AD5), U31.11 (A4), U32.11 (A4), U33.11 (A4), U34.11 (A4), U35.11 (A4), U36.2 (DIN), U36.11 (A4), U37.11 (A4), U38.11 (A4)
WD6: U30.4 (AD6), U31.10 (A5), U32.10 (A5), U33.10 (A5), U34.10 (A5), U35.10 (A5), U36.10 (A5), U37.2 (DIN), U37.10 (A5), U38.10 (A5)
WD7: U30.3 (AD7), U31.13 (A6), U32.13 (A6), U33.13 (A6), U34.13 (A6), U35.13 (A6), U36.13 (A6), U37.13 (A6), U38.2 (DIN), U38.13 (A6)
WE\: R37.2, U8.3 (~WE), U9.3 (~WE), U10.3 (~WE), U11.3 (~WE), U12.3 (~WE), U13.3 (~WE), U14.3 (~WE), U15.3 (~WE), U46.4
WR-D\: SLOT1.13, SLOT2.13, U28.9, U40.11 (O5b), U45.2 (A1)
WR\: U3.22 (~WR~), U40.12 (I5), U43.13
Y: J1.1 (In), JN10.3, R60.1, U30.36 (Y)
Y2\: U22.13 (O2), U45.4 (E1), U45.5 (E2)
Y3\: U22.12 (O3), U43.9, U43.12
Y4\: U22.11 (O4), U28.1, U41.10 (I4)
Y5\: U22.10 (O5), U28.10, U28.12, U47.13

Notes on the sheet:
LED CAPS LOCK
KEYBOARD MATRIX
CENTRONICS 14pin PRINTER
T=in / S=out / G=massa

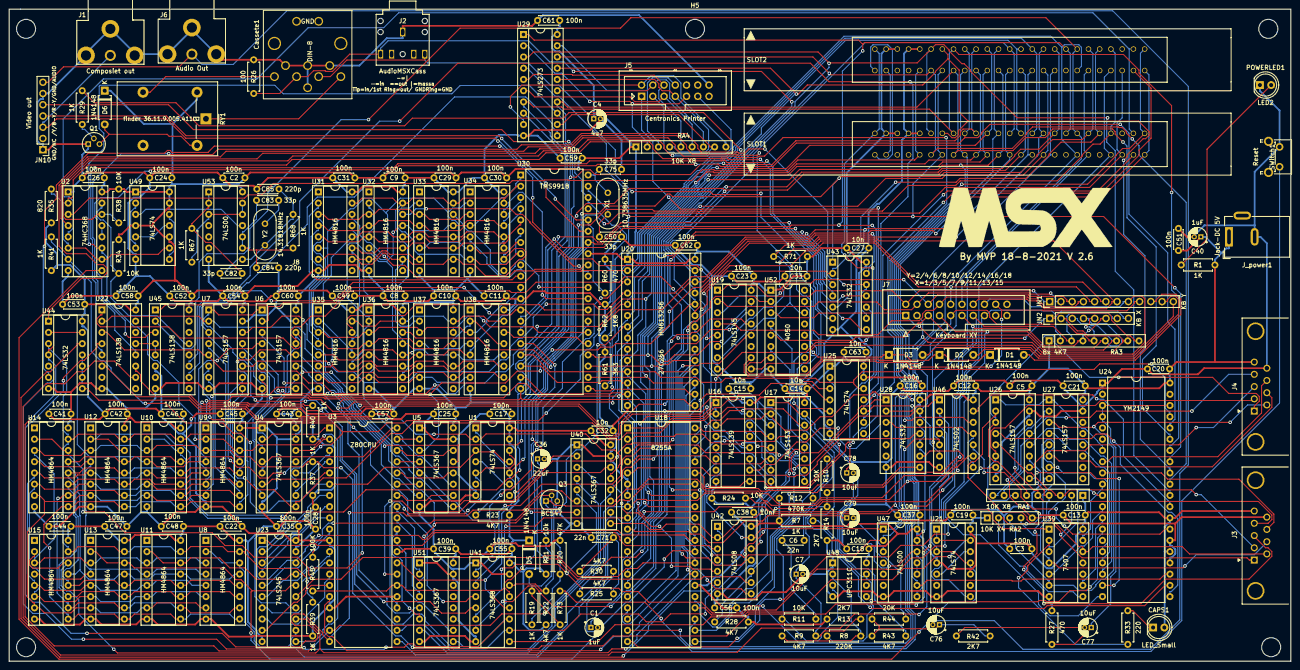
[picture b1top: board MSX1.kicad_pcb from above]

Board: 2 copper layers, 289.6 x 147.3 mm, 200 parts (0 on the bottom side), 265 nets.

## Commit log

2021-08-21 Update LICENSE
